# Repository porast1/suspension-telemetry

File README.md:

# suspension-telemetry
contact: patryk.grzywnowicz@gmail.com

The project consists in creating a system for testing suspension work and suggesting better settings. I love extreme cycling so came up with the idea out of passion and curiosity :)

The general concept of the idea, the embedded part:
- Using linear potentiometers will take place the main travel measurement
- Pressure sensors will monitor suspension progression
- Brake force measurment (using tensometers) for Braking statistics (not suported yet on GUI)
- The accelerometer will monitor overloads for a given setting,
- Recording of measurement data on the sd card
- LCD menu with buttons
- IOT (maybe)
- PCB project
- Enclosure
  
The most interesting part, data science:
- Setting up the server using the python streamlit and bokeh library
- Determination of the linear regression curve for the rebound/compression speed (curves from the front and rear suspension should have a similar slope)
- Histograms for individual speeds depending on the suspension travel used (in theory, they should be a normal Gaussian distribution curve)
- Calculation of the derivative over time to obtain acceleration on the shock absorber shaft at a particular moment of the stroke
- Calculation suspension progression
- FFT for frequency separation
- Many more methods of data analysis, you'll see soon :)

 Software architecture:
- The project uses FREERTOS and the board is stm32 nucleo f446RE.
- In python the time base will be generated using the amount of measurements. Currently, the timer triggers the ADC converter with DMA with a frequency of 5ms. I implemented a ping pong buffer to be able to process and save half of the buffer to the SD card without interrupting the ADC measurement, read-write synchronization is done using a binary semaphore.
- When measurement starts, fat32 file system creates new folder and files.
- I used switch-case to implement the menu, a new flag is set each time the button is invoked.
- Usb OTG for file sharing

Currently, the menu has 4 options:
1. Sensor calibration after installation - initial travel
2. Measurement of static deflection/sag - the LCD display shows the percentage of travel, for shock absorbers rear front and pressure values
3. Continuous measurement with recording on the SD card
4. Start menu

run GUI:
  - install python (3.11.4) and add to systemPATH as python
  - in bash runGUI.sh

STM project:
  - You need to setup project, I don't know why it's not import as it is
  - Generate code from .IOC and copy files from Core/src and inc
  - I changed some generated files related to fat32 and usb - compare changes and copy
  - Build
    
PCB project:
  - Use KiCad 7 to open

Enclosure:
  - standard .step file you can use freecad

Things that can be improved:
Embedded:
  - You can better organize file handling, e.g. opening and closing.
  - Separate the code from src and inc as separate packages for one functionality
  - The PCB diagram has the ability to communicate on 4 data lines, currently only 1 data line is configured in CubeMx. I had problems with the stm driver, maybe they improved it in newer fw versions.
  - Quite long detection of the connected device by the PC - currently about 8 seconds, not much, but I can complain :)
  - You can do some light refactoring of the code. The season was chasing me and I was actually the last one to do it :)
  - If you want to have pressure and braking statistics, you must purchase appropriate sensors. Writing to the device is supported after defining two parameters responsible for activation.
    
  PCB:
  - So far I have no objections
    
  GUI:
  - Without any objections

Images

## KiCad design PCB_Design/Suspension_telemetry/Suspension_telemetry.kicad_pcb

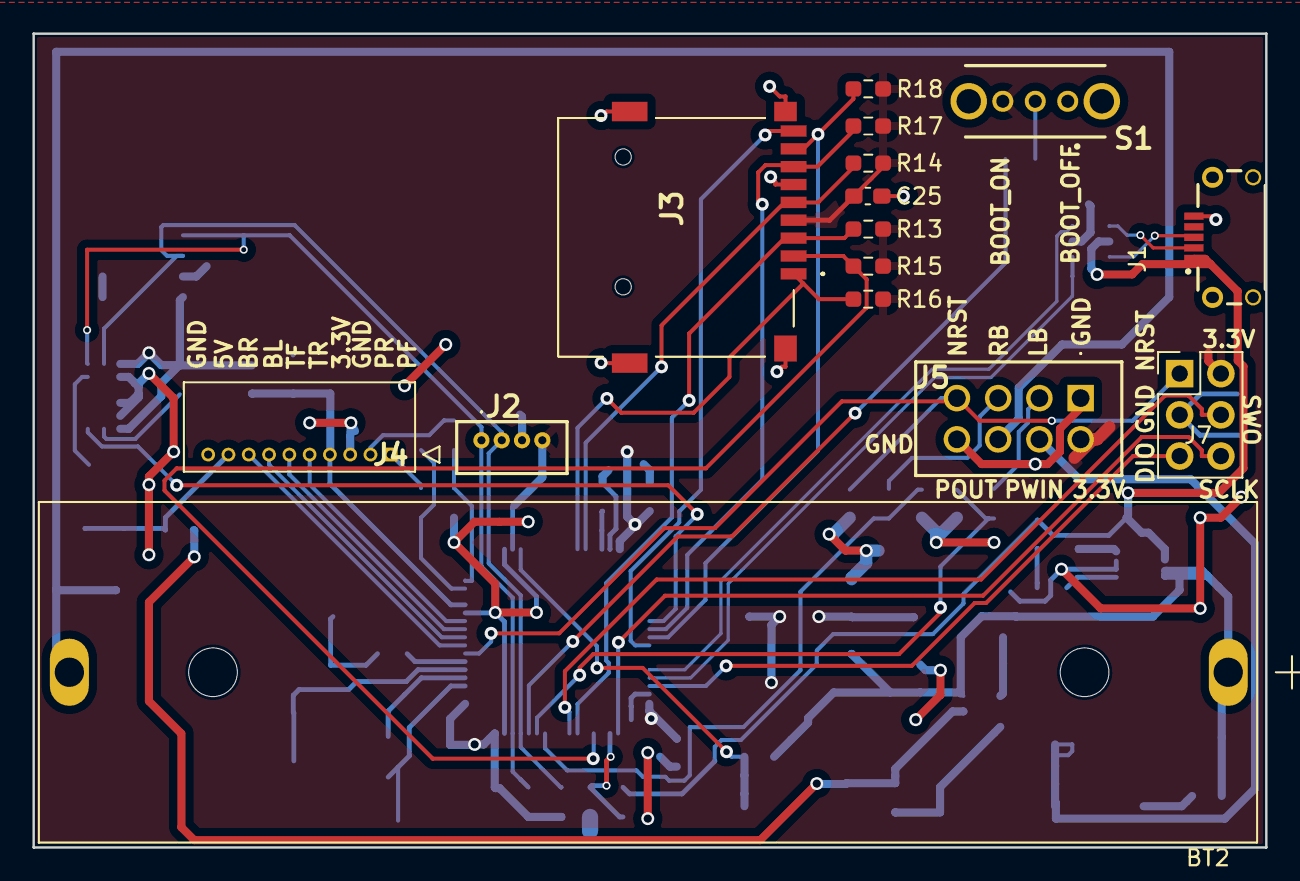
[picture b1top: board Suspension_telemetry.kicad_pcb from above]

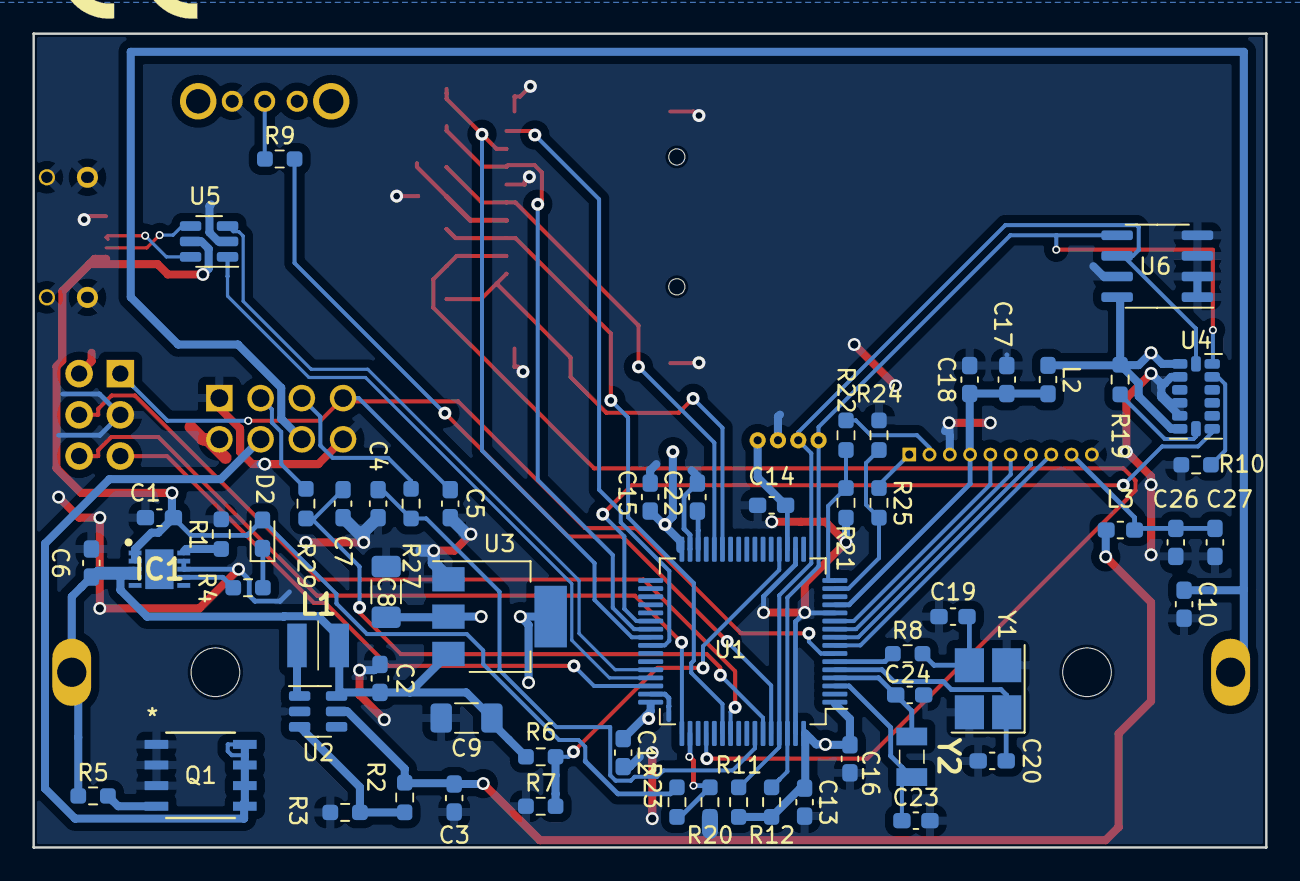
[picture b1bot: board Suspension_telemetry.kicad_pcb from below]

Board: 2 copper layers, 75.9 x 50.1 mm, 77 parts (62 on the bottom side), 57 nets.

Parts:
BT2: BK-18650-PC2; BAT_BK-18650-PC2
C1, C2, C3, C6, C17, C26: 1uF; C_0603_1608Metric_Pad1.08x0.95mm_HandSolder
C4, C5, C7, C10, C13, C14, C15, C16, C25: 100n; C_0603_1608Metric_Pad1.08x0.95mm_HandSolder
C8, C9: 10uF; C_1206_3216Metric_Pad1.33x1.80mm_HandSolder
C12, C22: 4,7uF; C_0603_1608Metric_Pad1.08x0.95mm_HandSolder
C18, C27: 10n; C_0603_1608Metric_Pad1.08x0.95mm_HandSolder
C19, C20, C23, C24: 8p; C_0603_1608Metric_Pad1.08x0.95mm_HandSolder
D2: LED_Small; LED_0603_1608Metric_Pad1.05x0.95mm_HandSolder
IC1: MCP73114-0NSI_MF; SON50P300X300X100-11N-D
J1: USB3505-30-A_REVA4; GCT_USB3505-30-A_REVA4
J2: 125SH-A-04-TS; 125SHA04TS
J3: 112J-TDAR-R01; 112JTDARR01
J4: 530481010
J5: 280384-1; 2803841
J7: Conn_02x03_Top_Bottom; PinHeader_2x03_P2.54mm_Vertical
L1: LQH3NPZ100MJRL; LQH3NPN100MJRL
L2, L3: 39n; L_0603_1608Metric_Pad1.05x0.95mm_HandSolder
N1, N2, N3: Housing; CE-Logo_8.5x6mm_SilkScreen
Q1: AOSP32368; SO8SOP-8L_AOS
R1: 1.1k; R_0603_1608Metric_Pad0.98x0.95mm_HandSolder
R2: 360k; R_0603_1608Metric_Pad0.98x0.95mm_HandSolder
R3: 68k; R_0603_1608Metric_Pad0.98x0.95mm_HandSolder
R4, R27, R29: 1k; R_0603_1608Metric_Pad0.98x0.95mm_HandSolder
R5, R9, R10, R13, R14, R15, R16, R17, R18: 10k; R_0603_1608Metric_Pad0.98x0.95mm_HandSolder
R6, R7: 100k; R_0603_1608Metric_Pad0.98x0.95mm_HandSolder
R8: 47; R_0603_1608Metric_Pad0.98x0.95mm_HandSolder
R11, R12: 2k2; R_0603_1608Metric_Pad0.98x0.95mm_HandSolder
R19, R22, R23, R25: 4,7k; R_0603_1608Metric_Pad0.98x0.95mm_HandSolder
R20, R21, R24: 6,8k; R_0603_1608Metric_Pad0.98x0.95mm_HandSolder
S1: OS102011MA1QN1
U1: STM32F446RET6; LQFP-64_10x10mm_P0.5mm
U2: TLV61046ADB; SOT-23-6
U3: LM1117MP-3.3; SOT-223-3_TabPin2
U4: ADXL343; LGA-14_3x5mm_P0.8mm_LayoutBorder1x6y
U5: USBLC6-2SC6; SOT-23-6
U6: AT24CS254-SSHM; SOIC-8_3.9x4.9mm_P1.27mm
Y1: Crystal_GND24_Small; Crystal_SMD_3225-4Pin_3.2x2.5mm_HandSoldering
Y2: ABS07-32.768KHZ-9-T; ABS07

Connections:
5V_USB: C1.1, D2.2 (A), IC1.1 (VDD_1), IC1.2 (VDD_2), J1.1 (VCC), R23.1, U5.5 (VBUS)
+3.3V: C8.1, C12.1, C13.1, C14.1, C15.1, C16.1, C25.1, J2.4, J3.4 (VDD), J5.2, J7.2, L2.1, R11.2, R12.2, R13.2, R14.2, R15.2, R16.2, R17.2, R18.2, R19.1, S1.3, U1.1 (VBAT), U1.19 (VDD), U1.32 (VDD), U1.48 (VDD), U1.64 (VDD), U3.2 (VO), U4.1 (Vdd_I/O), U4.6 (Vs), U6.8 (VCC)
+3.3VA: C17.1, C18.1, J4.4, L2.2, U1.13 (VDDA)
+5V: C3.2, L3.1, R2.1, U2.5 (VOUT)
+5VA: C26.1, C27.1, J4.9, L3.2
/Power_Stabilizer_3_3V/V_in_P: BT2.+, C2.2, C6.1, C9.1, IC1.3 (VBAT_1), IC1.4 (VBAT_2), L1.1, R5.1, R6.2, U2.6 (VI), U3.3 (VI)
ACCELEROMETER_INT0: U1.38 (PC7), U4.8 (INT1)
BATTERY_LEVEL: R6.1, R7.2, U1.20 (PA4)
BOOT: R9.2, U1.60 (BOOT0)
BRAKE_SENSOR_LEFT: J4.7, U1.9 (PC1)
BRAKE_SENSOR_RIGHT: J4.8, U1.8 (PC0)
CHARGE_DETECTION: R20.1, R23.2, U1.50 (PA15)
DATAN: J1.2 (D-), U5.4 (I/O2)
DATAP: J1.3 (D+), U5.6 (I/O1)
GND: C1.2, C2.1, C3.1, C4.2, C5.2, C6.2, C7.2, C8.2, C9.2, C10.2, C12.2, C13.2, C14.2, C15.2, C16.2, C17.2, C18.2, C19.2, C20.2, C22.2, C23.2, C24.2, C25.2, C26.2, C27.2, IC1.8 (VSS_1), IC1.9 (VSS_2), J1.5 (GND), J1.S1 (SHIELD), J1.S2 (SHIELD), J1.S3 (SHIELD), J1.S4 (SHIELD), J2.3, J3.6 (VSS), J3.G1 (GROUND), J3.MP1, J3.MP2, J3.MP3, J4.3, J4.10, J5.1, J5.8, J7.3, Q1.1, Q1.2, Q1.3, R1.2, R3.1, R7.1, R10.1, R20.2, R21.2, R24.2, S1.1, U1.12 (VSSA), U1.18 (VSS), U1.31 (VSS), U1.47 (VSS), U1.63 (VSS), U2.2 (GND), U3.1 (GND), U4.2 (GND), U4.4 (GND), U4.5 (GND), U5.2 (GND), U6.1 (A0), U6.2 (A1), U6.3 (A2), U6.4 (GND), U6.7 (WP), Y1.2, Y1.4
HSE_IN: C20.1, U1.5 (PH0), Y1.1
HSE_OUT: R8.1, U1.6 (PH1)
I2C1_SCL: J2.2, R11.1, U1.61 (PB8), U4.14 (SCL/SCLK), U6.6 (SCL)
I2C1_SDA: J2.1, R12.1, U1.62 (PB9), U4.13 (SDA/SDI/SDIO), U6.5 (SDA)
LB_PRE_DEB: J5.3, R29.2
LEFT_BUTTON: C7.1, R29.1, U1.59 (PB7)
NRST: C5.1, J5.7, J7.1, U1.7 (NRST)
unnamed: C19.1, R8.2, Y1.3
unnamed: D2.1 (K), R4.2
unnamed: IC1.10 (PROG), R1.1
unnamed: IC1.7 (STAT), R4.1
unnamed: Q1.4, R5.2
unnamed: R9.1, S1.2
unnamed: C22.1, U1.30 (VCAP_1)
unnamed: R2.2, R3.2, U2.3 (FB)
unnamed: L1.2, U2.1 (SW)
unnamed: R10.2, U4.12 (SDO/ADDR)
unnamed: R19.2, U4.7 (~CS)
PRESSURE_FRONT_OUT: J4.1, R25.1
PRESSURE_REAR_OUT: J4.2, R22.1
PRESSURE_SENSOR_FRONT: R24.1, R25.2, U1.15 (PA1)
PRESSURE_SENSOR_REAR: R21.1, R22.2, U1.16 (PA2)
PWR_SWITCH_IN: J5.4, Q1.5, Q1.6, Q1.7, Q1.8
PWR_SWITCH_OUT: BT2.-, C10.1, J5.6
RB_PRE_DEB: J5.5, R27.2
RCC_32_IN: C23.1, U1.3 (PC14), Y2.1
RCC_32_OUT: C24.1, U1.4 (PC15), Y2.2
RIGHT_BUTTON: C4.1, R27.1, U1.58 (PB6)
SDIO_CK: J3.5 (CLK), R14.1, U1.28 (PB2)
SDIO_CMD: J3.3 (CMD), R13.1, U1.54 (PD2)
SDIO_D0: J3.7 (DAT0), R17.1, U1.39 (PC8)
SDIO_D1: J3.8 (DAT1), R18.1, U1.40 (PC9)
SDIO_D2: J3.1 (DAT2), R16.1, U1.27 (PB1)
SDIO_D3: J3.2 (CD/DAT3), R15.1, U1.52 (PC11)
SD_detection: J3.CD1 (CARD_DETECTION), U1.41 (PA8)
SWDCLK: J7.6, U1.49 (PA14)
SWDIO: J7.5, U1.46 (PA13)
SWO: J7.4, U1.55 (PB3)
TRAVEL_SENOR_REAR: J4.5, U1.11 (PC3)
TRAVEL_SENSOR_FRONT: J4.6, U1.10 (PC2)
USB_OTG_FS_D+: U1.45 (PA12), U5.1 (I/O1)
USB_OTG_FS_D-: U1.44 (PA11), U5.3 (I/O2)

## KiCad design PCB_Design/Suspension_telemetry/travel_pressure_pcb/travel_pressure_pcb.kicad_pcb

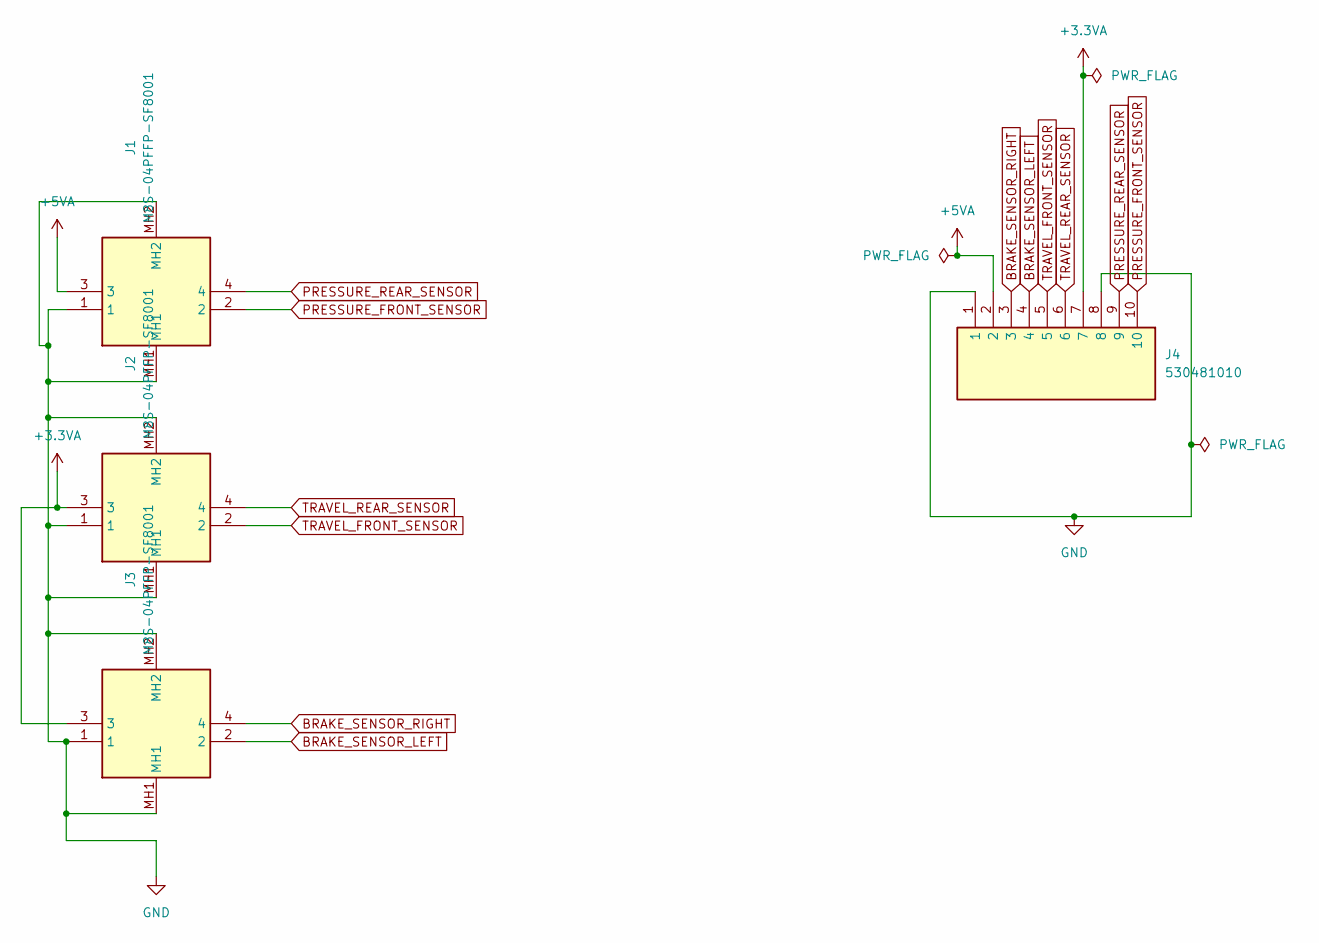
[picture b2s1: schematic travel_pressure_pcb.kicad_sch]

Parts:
J1, J2, J3: M8S-04PFFP-SF8001; M8S04PFFPSF8001; Manufacturer_Part_Number M8S-04PFFP-SF8001
J4: 530481010; Manufacturer_Part_Number 530481010

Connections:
+3.3VA: J2.3, J3.3, J4.7
+5VA: J1.3, J4.2
BRAKE_SENSOR_LEFT: J3.2, J4.4
BRAKE_SENSOR_RIGHT: J3.4, J4.3
GND: J1.1, J1.MH1, J1.MH2, J2.1, J2.MH1, J2.MH2, J3.1, J3.MH1, J3.MH2, J4.1, J4.8
PRESSURE_FRONT_SENSOR: J1.2, J4.10
PRESSURE_REAR_SENSOR: J1.4, J4.9
TRAVEL_FRONT_SENSOR: J2.2, J4.5
TRAVEL_REAR_SENSOR: J2.4, J4.6

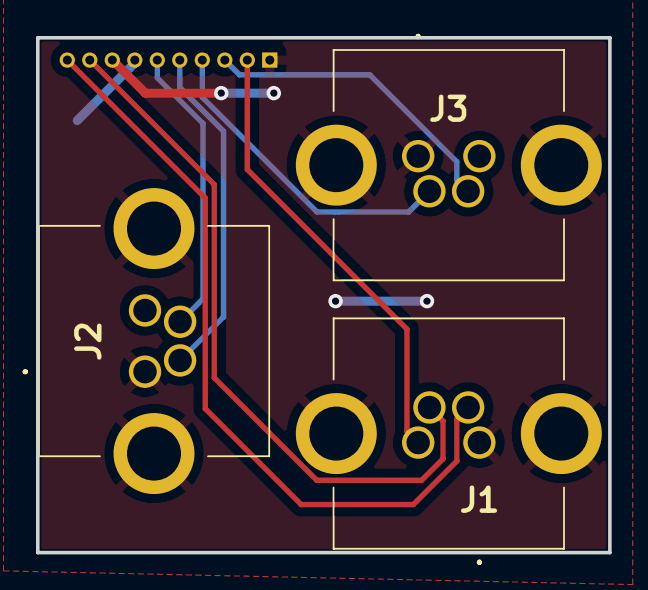
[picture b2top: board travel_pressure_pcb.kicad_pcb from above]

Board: 2 copper layers, 31.8 x 28.6 mm, 4 parts (1 on the bottom side), 9 nets.

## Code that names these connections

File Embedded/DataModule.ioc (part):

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Mcu.Name=STM32F446R(C-E)Tx
Mcu.Package=LQFP64
Mcu.UserName=STM32F446RETx
PA1.GPIOParameters=GPIO_Label
PA1.GPIO_Label=PRESSURE_SENSOR_FRONT
PA1.Signal=ADCx_IN1
PA11.Mode=Device_Only
PA11.Signal=USB_OTG_FS_DM
PA12.Mode=Device_Only
PA12.Signal=USB_OTG_FS_DP
PA13.GPIOParameters=GPIO_Label
PA13.GPIO_Label=TMS
PA13.Mode=Serial_Wire
PA13.Signal=SYS_JTMS-SWDIO
PA14.GPIOParameters=GPIO_Label
PA14.GPIO_Label=TCK
PA14.Mode=Serial_Wire
PA14.Signal=SYS_JTCK-SWCLK
PA15.GPIOParameters=GPIO_Label
PA15.GPIO_Label=CHARGE_DETECTION
PA15.Signal=GPIO_Input
PA2.GPIOParameters=GPIO_Label
PA2.GPIO_Label=PRESSURE_SENSOR_REAR
PA2.Signal=ADCx_IN2
PA4.GPIOParameters=GPIO_Label
PA4.GPIO_Label=BATTERY_LEVEL
PA4.Signal=ADCx_IN4
PA8.GPIOParameters=GPIO_PuPd,GPIO_Label
PA8.GPIO_Label=SD_detection
PA8.GPIO_PuPd=GPIO_PULLUP
PA8.Signal=GPIO_Input
PB2.Mode=SD_1_bit
PB2.Signal=SDIO_CK
PB3.GPIOParameters=GPIO_Label
PB3.GPIO_Label=SWO
PB3.Signal=SYS_JTDO-SWO
PB6.GPIOParameters=GPIO_PuPd,GPIO_Label
PB6.GPIO_Label=RIGHT_BUTTON
PB6.GPIO_PuPd=GPIO_PULLUP
PB6.Signal=GPIO_Input
PB7.GPIOParameters=GPIO_PuPd,GPIO_Label
PB7.GPIO_Label=LEFT_BUTTON
PB7.GPIO_PuPd=GPIO_PULLUP
PB7.Signal=GPIO_Input
PB8.Mode=I2C
PB8.Signal=I2C1_SCL
PB9.Mode=I2C
PB9.Signal=I2C1_SDA
PC0.GPIOParameters=GPIO_Label
PC0.GPIO_Label=BRAKE_SENSOR_RIGHT
PC0.Signal=ADCx_IN10
PC1.GPIOParameters=GPIO_Label
PC1.GPIO_Label=BRAKE_SENSOR_LEFT
PC1.Signal=ADCx_IN11
PC14-OSC32_IN.Mode=LSE-External-Oscillator
PC14-OSC32_IN.Signal=RCC_OSC32_IN
PC15-OSC32_OUT.Mode=LSE-External-Oscillator
PC15-OSC32_OUT.Signal=RCC_OSC32_OUT
PC2.GPIOParameters=GPIO_Label
PC2.GPIO_Label=TRAVEL_SENSOR_FRONT
PC2.Signal=ADCx_IN12
PC3.GPIOParameters=GPIO_Label
PC3.GPIO_Label=TRAVEL_SENSOR_REAR
PC3.Signal=ADCx_IN13
PC7.GPIOParameters=GPIO_Label
PC7.GPIO_Label=ACCELEROMETER_INT0
PC7.Signal=GPXTI7
PC8.GPIOParameters=GPIO_PuPd
PC8.GPIO_PuPd=GPIO_PULLUP
PC8.Mode=SD_1_bit
PC8.Signal=SDIO_D0
PC9.GPIOParameters=GPIO_PuPd
PC9.GPIO_PuPd=GPIO_PULLUP
PC9.Signal=SDIO_D1
PD2.GPIOParameters=GPIO_PuPd
PD2.GPIO_PuPd=GPIO_PULLUP
PD2.Mode=SD_1_bit
PD2.Signal=SDIO_CMD
PH0-OSC_IN.Mode=HSE-External-Oscillator
PH0-OSC_IN.Signal=RCC_OSC_IN
PH1-OSC_OUT.Mode=HSE-External-Oscillator
PH1-OSC_OUT.Signal=RCC_OSC_OUT
RCC.HSE_VALUE=16000000
RCC.SYSCLKFreq_VALUE=168000000
RCC.SYSCLKSource=RCC_SYSCLKSOURCE_PLLCLK
board=NUCLEO-F446RE
boardIOC=true

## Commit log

2023-07-15 test
2023-07-15 data_acquisition_module: Init stm32 project
2023-07-16 data_acquisition_module: working two travel sensor DMA
2023-07-20 data_acquisition_module: working adc in 5ms period, add fat32 write/read
2023-07-20 data_acquisition_module: grooming code v1
2023-07-20 checking main before create branch
2023-07-26 button_driver: initial menu plus buttons
2023-07-27 button_driver: add separate folder per measurment
2023-07-27 nothing special
2023-07-27 add formatter
2023-07-31 pressure_sensor: add presure sensors plus calibration
2023-07-31 checking before merge
2023-08-06 lcd_display: working lcd in i2c
2023-08-06 lcd_display: menu working fine
2023-09-26 some changes
2023-10-05 finished Schematic, PCB creation
2023-10-06 PCB: Finished
2023-10-08 init gui
2023-10-08 Added Dev Container Folder
2023-10-08 add requirements.txt
2023-10-08 add some requirements
2023-10-08 change location
2023-10-10 Initial:GUI
2023-10-16 GUI:all charts done
2023-10-17 finished GUI
2023-10-17 repair velocity chart
2023-11-04 before pcb v2
2023-11-22 pcv v2 finished
2023-12-05 zrobiłem burdel w branch, ale płytka dziala
2023-12-13 resolved clock issues
2023-12-13 changed, not tested
2023-12-28 adding swnsor mounts
2024-03-05 new code for gui
2024-03-05 change git ignore
2024-03-15 repo pre cleaned
2024-03-17 Updated .gitignore and removed ignored files
2024-03-18 cleanup repository
2024-03-18 improve api
2024-03-27 api and refactor done
2024-03-27 add json run from venv
2024-03-27 add script
2024-03-27 realocate reg.txt test
2024-03-27 Updated .gitignore
2024-03-27 git ignore update
2024-03-27 git ignore update v2
2024-03-28 add demo data
2024-03-28 add images
2024-03-29 Create LICENSE
